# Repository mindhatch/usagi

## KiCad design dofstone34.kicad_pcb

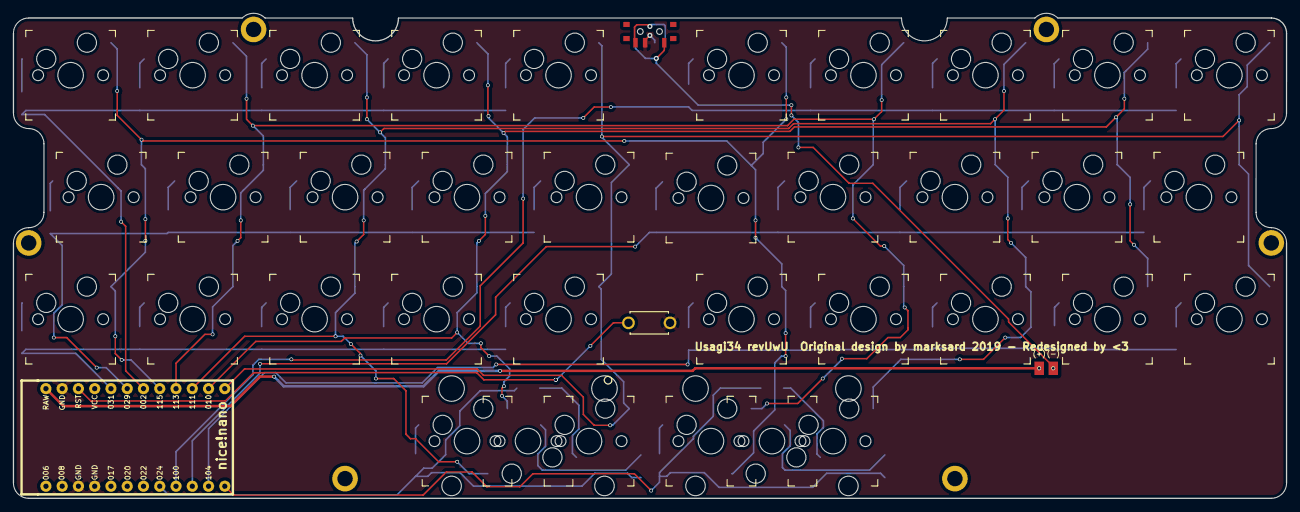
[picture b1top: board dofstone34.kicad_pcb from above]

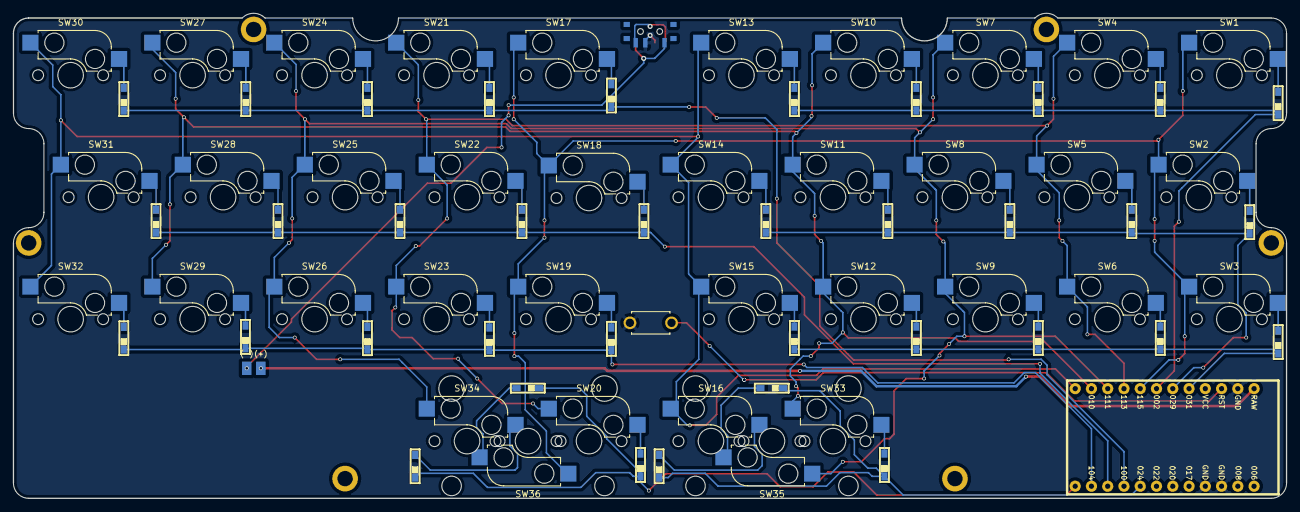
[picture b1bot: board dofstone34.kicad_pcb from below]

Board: 2 copper layers, 198.8 x 75.7 mm, 76 parts (36 on the bottom side), 53 nets.

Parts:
BT1: Battery_Cell; Battery_pads_reversible
D1, D2, D3, D4, D5, D6, D7, D8, D9, D10, D11, D12, D13, D14, D15, D17, D18, D19, D20, D20#2, D20#3, D20#4, D21, D22, D23, D24, D25, D26, D27, D28, D29, D30, D31, D32, D34, D34#2: D; D3_SMD_only_front
PSW1: SW_SPDT; Power_reversible
SW1, SW2, SW3, SW4, SW5, SW6, SW7, SW8, SW9, SW10, SW11, SW12, SW13, SW14, SW15, SW16, SW17, SW18, SW19, SW20, SW21, SW22, SW23, SW24, SW25, SW26, SW27, SW28, SW29, SW30, SW31, SW32, SW33, SW34, SW35, SW36: SW_PUSH; Kailh_socket_MX
SW16#2: SW_Push; ResetSW
U1: nice_nano

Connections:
BATT: BT1.2 (-), PSW1.1 (A)
GND: PSW1.2 (B), SW16#2.2, U1.3, U1.4, U1.23
unnamed: D1.2, SW1.2
unnamed: D2.2, SW2.2
unnamed: D3.2, SW3.2
unnamed: D4.2, SW4.2
unnamed: D5.2, SW5.2
unnamed: D6.2, SW6.2
unnamed: D7.2, SW7.2
unnamed: D8.2, SW8.2
unnamed: D9.2, SW9.2
unnamed: D10.2, SW10.2
unnamed: D11.2, SW11.2
unnamed: D12.2, SW12.2
unnamed: D13.2, SW13.2
unnamed: D14.2, SW14.2
unnamed: D15.2, SW15.2
unnamed: D34#2.2, SW16.2
unnamed: D17.2, SW17.2
unnamed: D18.2, SW18.2
unnamed: D19.2, SW19.2
unnamed: D20.2, SW20.2
unnamed: D21.2, SW21.2
unnamed: D22.2, SW22.2
unnamed: D23.2, SW23.2
unnamed: D24.2, SW24.2
unnamed: D25.2, SW25.2
unnamed: D26.2, SW26.2
unnamed: D27.2, SW27.2
unnamed: D28.2, SW28.2
unnamed: D29.2, SW29.2
unnamed: D30.2, SW30.2
unnamed: D31.2, SW31.2
unnamed: D32.2, SW32.2
unnamed: D20#2.2, SW33.2
unnamed: D34.2, SW34.2
unnamed: D20#4.2, SW35.2
unnamed: D20#3.2, SW36.2
RST: SW16#2.1, U1.22
col0: SW1.1, SW2.1, SW3.1, SW17.1, SW18.1, SW19.1, SW36.1, U1.17
col1: SW4.1, SW5.1, SW6.1, SW20.1, SW21.1, SW22.1, SW23.1, U1.16
col2: SW7.1, SW8.1, SW9.1, SW24.1, SW25.1, SW26.1, SW34.1, SW35.1, U1.15
col3: SW10.1, SW11.1, SW12.1, SW27.1, SW28.1, SW29.1, SW33.1, U1.14
col4: SW13.1, SW14.1, SW15.1, SW16.1, SW30.1, SW31.1, SW32.1, U1.13
raw: BT1.1 (+), U1.24
row0: D1.1, D4.1, D7.1, D10.1, D13.1, U1.18
row1: D2.1, D5.1, D8.1, D11.1, D14.1, U1.19
row2: D3.1, D6.1, D9.1, D12.1, D15.1, U1.20
row3: D20#2.1, D20#4.1, D34#2.1, U1.8
row4: D17.1, D21.1, D24.1, D27.1, D30.1, U1.9
row5: D18.1, D22.1, D25.1, D28.1, D31.1, U1.10
row6: D19.1, D23.1, D26.1, D29.1, D32.1, U1.11
row7: D20.1, D20#3.1, D34.1, U1.12
